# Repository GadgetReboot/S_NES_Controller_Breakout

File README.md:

# S_NES_Controller_Breakout
Breakout board to decode NES or SNES controller buttons as separate GPIO outputs from ATTiny26
<br><br><br><br>

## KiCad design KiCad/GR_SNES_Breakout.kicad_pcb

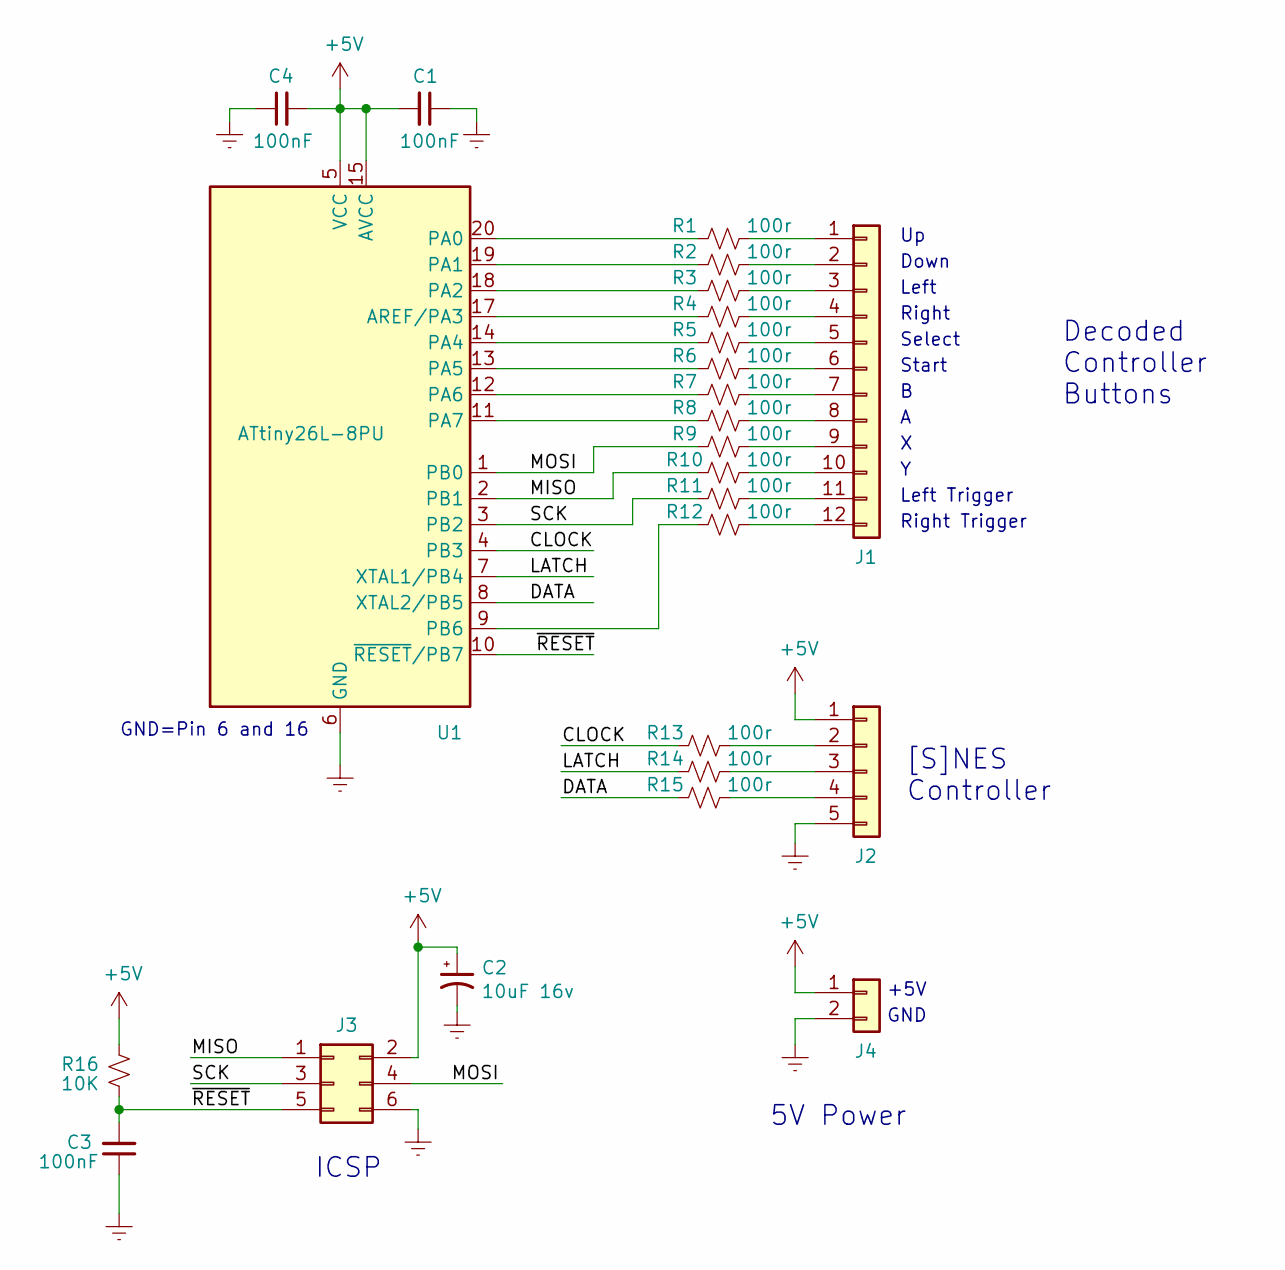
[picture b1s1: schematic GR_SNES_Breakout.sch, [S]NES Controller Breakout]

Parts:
C1, C3, C4: 100nF; C_Disc_D3.8mm_W2.6mm_P2.50mm
C2: 10uF 16v; CP_Radial_D5.0mm_P2.50mm
J1: Conn_01x12; PinHeader_1x12_P2.54mm_Vertical
J2: Conn_01x05; PinHeader_1x05_P2.54mm_Vertical
J3: Conn_02x03_Odd_Even; PinHeader_2x03_P2.54mm_Vertical
J4: Conn_01x02; PinHeader_1x02_P2.54mm_Vertical
R1, R2, R3, R4, R5, R6, R7, R8, R9, R10, R11, R12, R13, R14, R15: 100r; R_Axial_DIN0309_L9.0mm_D3.2mm_P12.70mm_Horizontal
R16: 10K; R_Axial_DIN0309_L9.0mm_D3.2mm_P12.70mm_Horizontal
U1: ATtiny26L-8PU; DIP-20_W7.62mm

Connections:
+5V: C1.2, C2.1, C4.2, J2.1, J3.2, J4.1, R16.1, U1.5 (VCC), U1.15 (AVCC)
/CLOCK: R13.1, U1.4 (PB3)
/DATA: R15.1, U1.8 (XTAL2/PB5)
/LATCH: R14.1, U1.7 (XTAL1/PB4)
/MISO: J3.1, R10.1, U1.2 (PB1)
/MOSI: J3.4, R9.1, U1.1 (PB0)
/SCK: J3.3, R11.1, U1.3 (PB2)
/~RESET: C3.2, J3.5, R16.2, U1.10 (~RESET~/PB7)
GNDREF: C1.1, C2.2, C3.1, C4.1, J2.5, J3.6, J4.2, U1.6 (GND), U1.16 (GND)
unnamed: J1.1, R1.2
unnamed: J1.2, R2.2
unnamed: J1.3, R3.2
unnamed: J1.4, R4.2
unnamed: J1.5, R5.2
unnamed: J1.6, R6.2
unnamed: J1.7, R7.2
unnamed: J1.8, R8.2
unnamed: J1.9, R9.2
unnamed: J1.10, R10.2
unnamed: J1.11, R11.2
unnamed: J1.12, R12.2
unnamed: J2.2, R13.2
unnamed: J2.3, R14.2
unnamed: J2.4, R15.2
unnamed: R1.1, U1.20 (PA0)
unnamed: R2.1, U1.19 (PA1)
unnamed: R3.1, U1.18 (PA2)
unnamed: R4.1, U1.17 (AREF/PA3)
unnamed: R5.1, U1.14 (PA4)
unnamed: R6.1, U1.13 (PA5)
unnamed: R7.1, U1.12 (PA6)
unnamed: R8.1, U1.11 (PA7)
unnamed: R12.1, U1.9 (PB6)

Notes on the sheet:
[S]NES Controller
GND=Pin 6 and 16
ICSP
Down
Left
Right
Select
Start
Left Trigger
Right Trigger
Decoded Controller Buttons
5V Power
+5V
GND

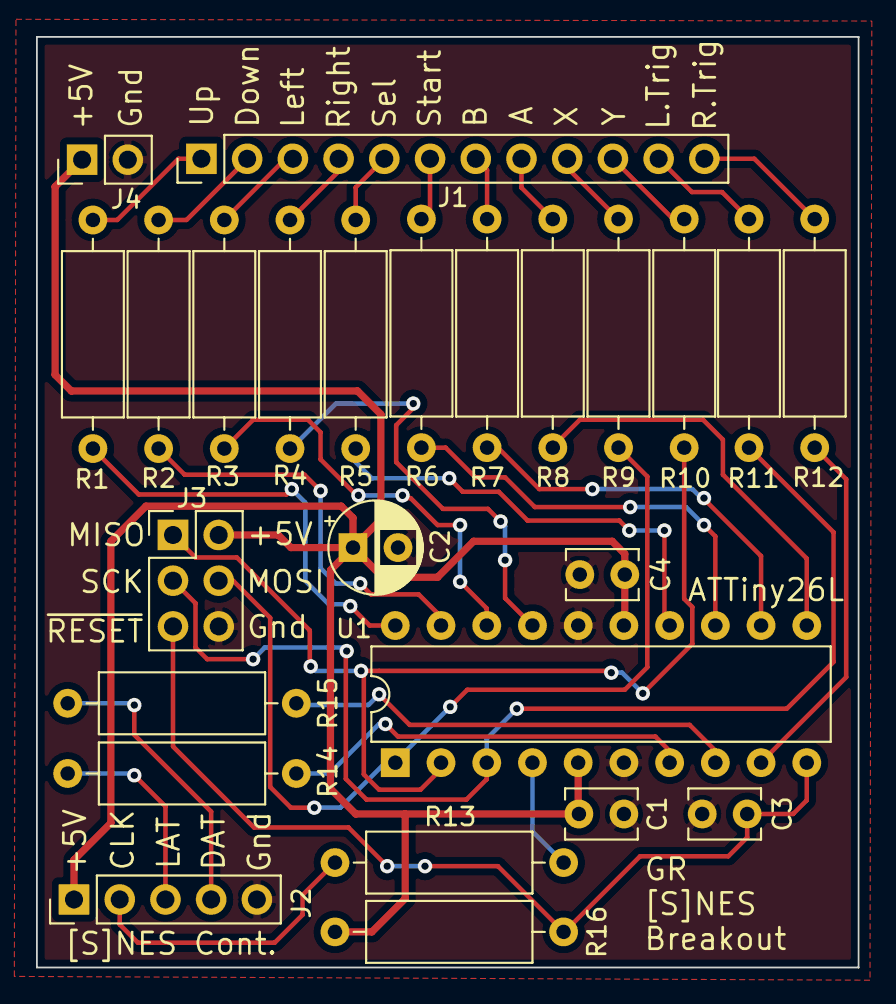
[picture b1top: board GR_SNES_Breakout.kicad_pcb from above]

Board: 2 copper layers, 45.7 x 51.7 mm, 25 parts (0 on the bottom side), 33 nets.

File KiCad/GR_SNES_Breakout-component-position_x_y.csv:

Ref,Val,Package,PosX,PosY,Rot,Side
"G***","LOGO","pcb way logo",-31.311000,14.229000,180.000000,bottom
"C1","100nF","C_Disc_D3.8mm_W2.6mm_P2.50mm",32.611000,8.529000,180.000000,top
"C2","10uF 16v","CP_Radial_D5.0mm_P2.50mm",17.561000,23.329000,0.000000,top
"C3","100nF","C_Disc_D3.8mm_W2.6mm_P2.50mm",36.961000,8.529000,0.000000,top
"C4","100nF","C_Disc_D3.8mm_W2.6mm_P2.50mm",30.161000,21.829000,0.000000,top
"J1","Conn_01x12","PinHeader_1x12_P2.54mm_Vertical",9.141000,44.929000,90.000000,top
"J2","Conn_01x05","PinHeader_1x05_P2.54mm_Vertical",2.061000,3.779000,90.000000,top
"J3","Conn_02x03_Odd_Even","PinHeader_2x03_P2.54mm_Vertical",7.561000,24.029000,0.000000,top
"J4","Conn_01x02","PinHeader_1x02_P2.54mm_Vertical",2.511000,44.879000,90.000000,top
"R1","100r","R_Axial_DIN0309_L9.0mm_D3.2mm_P12.70mm_Horizontal",3.111000,28.829000,90.000000,top
"R2","100r","R_Axial_DIN0309_L9.0mm_D3.2mm_P12.70mm_Horizontal",6.761000,28.829000,90.000000,top
"R3","100r","R_Axial_DIN0309_L9.0mm_D3.2mm_P12.70mm_Horizontal",10.411000,28.829000,90.000000,top
"R4","100r","R_Axial_DIN0309_L9.0mm_D3.2mm_P12.70mm_Horizontal",14.061000,28.829000,90.000000,top
"R5","100r","R_Axial_DIN0309_L9.0mm_D3.2mm_P12.70mm_Horizontal",17.711000,28.829000,90.000000,top
"R6","100r","R_Axial_DIN0309_L9.0mm_D3.2mm_P12.70mm_Horizontal",21.361000,28.879000,90.000000,top
"R7","100r","R_Axial_DIN0309_L9.0mm_D3.2mm_P12.70mm_Horizontal",25.011000,28.879000,90.000000,top
"R8","100r","R_Axial_DIN0309_L9.0mm_D3.2mm_P12.70mm_Horizontal",28.661000,28.879000,90.000000,top
"R9","100r","R_Axial_DIN0309_L9.0mm_D3.2mm_P12.70mm_Horizontal",32.311000,28.879000,90.000000,top
"R10","100r","R_Axial_DIN0309_L9.0mm_D3.2mm_P12.70mm_Horizontal",35.961000,28.879000,90.000000,top
"R11","100r","R_Axial_DIN0309_L9.0mm_D3.2mm_P12.70mm_Horizontal",39.561000,28.879000,90.000000,top
"R12","100r","R_Axial_DIN0309_L9.0mm_D3.2mm_P12.70mm_Horizontal",43.211000,28.879000,90.000000,top
"R13","100r","R_Axial_DIN0309_L9.0mm_D3.2mm_P12.70mm_Horizontal",29.261000,5.829000,180.000000,top
"R14","100r","R_Axial_DIN0309_L9.0mm_D3.2mm_P12.70mm_Horizontal",14.411000,10.779000,180.000000,top
"R15","100r","R_Axial_DIN0309_L9.0mm_D3.2mm_P12.70mm_Horizontal",14.411000,14.679000,180.000000,top
"R16","10K","R_Axial_DIN0309_L9.0mm_D3.2mm_P12.70mm_Horizontal",16.561000,1.979000,0.000000,top
"U1","ATtiny26L-8PU","DIP-20_W7.62mm",19.911000,11.379000,90.000000,top

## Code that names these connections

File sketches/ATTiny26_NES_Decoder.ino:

/*
  NES Controller Button Reader
  Target Device: ATTiny26L
  Tested with Arduino IDE 1.8.13
  Requires ATTinyCore board file v2 or later for ATTiny26 support:  https://github.com/SpenceKonde/ATTinyCore

  Controller Button States:
  nesRegister [7..0] = [Right, Left, Down, Up, Start, Select, B, A]

  NES controller pinout:
               _________
             /          |
            /        O  | Ground
           /            |
     +VCC  |  O      O  | Clock
           |            |
     N.C.  |  O      O  | Latch
           |            |
     N.C.  |  O      O  | Data Out (To NES)
           |____________|

  ATTinyCore Pin Map

  ATTiny26 GPIO    Arduino Pin Number
      PA0                0
      PA1                1
      PA2                2
      PA3                3
      PA4                4
      PA5                5
      PA6                6
      PA7                7
      PB0                8
      PB1                9
      PB2               10
      PB3               11
      PB4               12
      PB5               13
      PB6               14
      PB7               15  (RESET)


  Gadget Reboot
*/


// bit positions of each controller button in the status register
const int A_BUTTON         = 0;
const int B_BUTTON         = 1;
const int SELECT_BUTTON    = 2;
const int START_BUTTON     = 3;
const int UP_BUTTON        = 4;
const int DOWN_BUTTON      = 5;
const int LEFT_BUTTON      = 6;
const int RIGHT_BUTTON     = 7;

const int shiftDelay       = 20;    // delay in microseconds to help with shift register setup/hold timing

byte nesRegister           = 255;   // store button states. 0=pressed 1=released  default all released

// NES Pins
const int nesClock          = 11;    // NES controller 4021 clock pin
const int nesLatch          = 12;    // NES controller 4021 latch pin
const int nesData           = 13;    // NES controller 4021 data pin

// Output pins
const int outputLeft           = 2;   // outputs to show controller button activity
const int outputUp             = 0;
const int outputDn             = 1;
const int outputRight          = 3;
const int outputSelect         = 4;
const int outputStart          = 5;
const int outputB              = 6;
const int outputA              = 7;
const int outputX              = 8;
const int outputY              = 9;
const int outputLT             = 10;
const int outputRT             = 14;


void setup()
{
  // configure NES pins
  pinMode(nesData, INPUT_PULLUP);
  pinMode(nesClock, OUTPUT);
  pinMode(nesLatch, OUTPUT);

  digitalWrite(nesClock, LOW);      // NES control lines idle low
  digitalWrite(nesLatch, LOW);

  digitalWrite(outputLeft, HIGH);
  digitalWrite(outputUp, HIGH);
  digitalWrite(outputDn, HIGH);
  digitalWrite(outputRight, HIGH);
  digitalWrite(outputSelect, HIGH);
  digitalWrite(outputStart, HIGH);
  digitalWrite(outputA, HIGH);
  digitalWrite(outputB, HIGH);

  pinMode(outputLeft, OUTPUT);
  pinMode(outputUp, OUTPUT);
  pinMode(outputDn, OUTPUT);
  pinMode(outputRight, OUTPUT);
  pinMode(outputSelect, OUTPUT);
  pinMode(outputStart, OUTPUT);
  pinMode(outputA, OUTPUT);
  pinMode(outputB, OUTPUT);
  pinMode(outputX, INPUT);        // not used on NES
  pinMode(outputY, INPUT);        // not used on NES
  pinMode(outputLT, INPUT);       // not used on NES
  pinMode(outputRT, INPUT);       // not used on NES
}

void loop()
{
  // read the 8 controller buttons into the nesRegister
  // NES controller button states are loaded into the 4021 while nesLatch is high
  // When nesLatch goes low, the first data bit is shifted to nesData
  // Button data is shifted to nesData on each low to high transition of nesClock

  digitalWrite(nesLatch, HIGH);       // latch button states into shift register
  delayMicroseconds(shiftDelay);      // impose a delay to allow a setup and hold time for any 4021 pins
  digitalWrite(nesLatch, LOW);

  for (int x = 0; x <= 7; x++) {                    // read in the 8 controller buttons that were latched
    bitWrite(nesRegister, x, digitalRead(nesData)); // store the current button states into the nesRegister
    digitalWrite(nesClock, HIGH);                   // generate a clock pulse
    delayMicroseconds(shiftDelay);
    digitalWrite(nesClock, LOW);
  }

  // assign the 8 NES controller button states to the outputs.
  // 0 = button pressed so set output port low
  digitalWrite(outputLeft   , bitRead(nesRegister, LEFT_BUTTON));
  digitalWrite(outputUp     , bitRead(nesRegister, UP_BUTTON));
  digitalWrite(outputDn     , bitRead(nesRegister, DOWN_BUTTON));
  digitalWrite(outputRight  , bitRead(nesRegister, RIGHT_BUTTON));
  digitalWrite(outputSelect , bitRead(nesRegister, SELECT_BUTTON));
  digitalWrite(outputStart  , bitRead(nesRegister, START_BUTTON));
  digitalWrite(outputB      , bitRead(nesRegister, B_BUTTON));
  digitalWrite(outputA      , bitRead(nesRegister, A_BUTTON));

}
